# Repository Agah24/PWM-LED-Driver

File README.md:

# PWM-LED-Driver
Here is a KiCad Project for an PWM LED Driver to adjust its brightness

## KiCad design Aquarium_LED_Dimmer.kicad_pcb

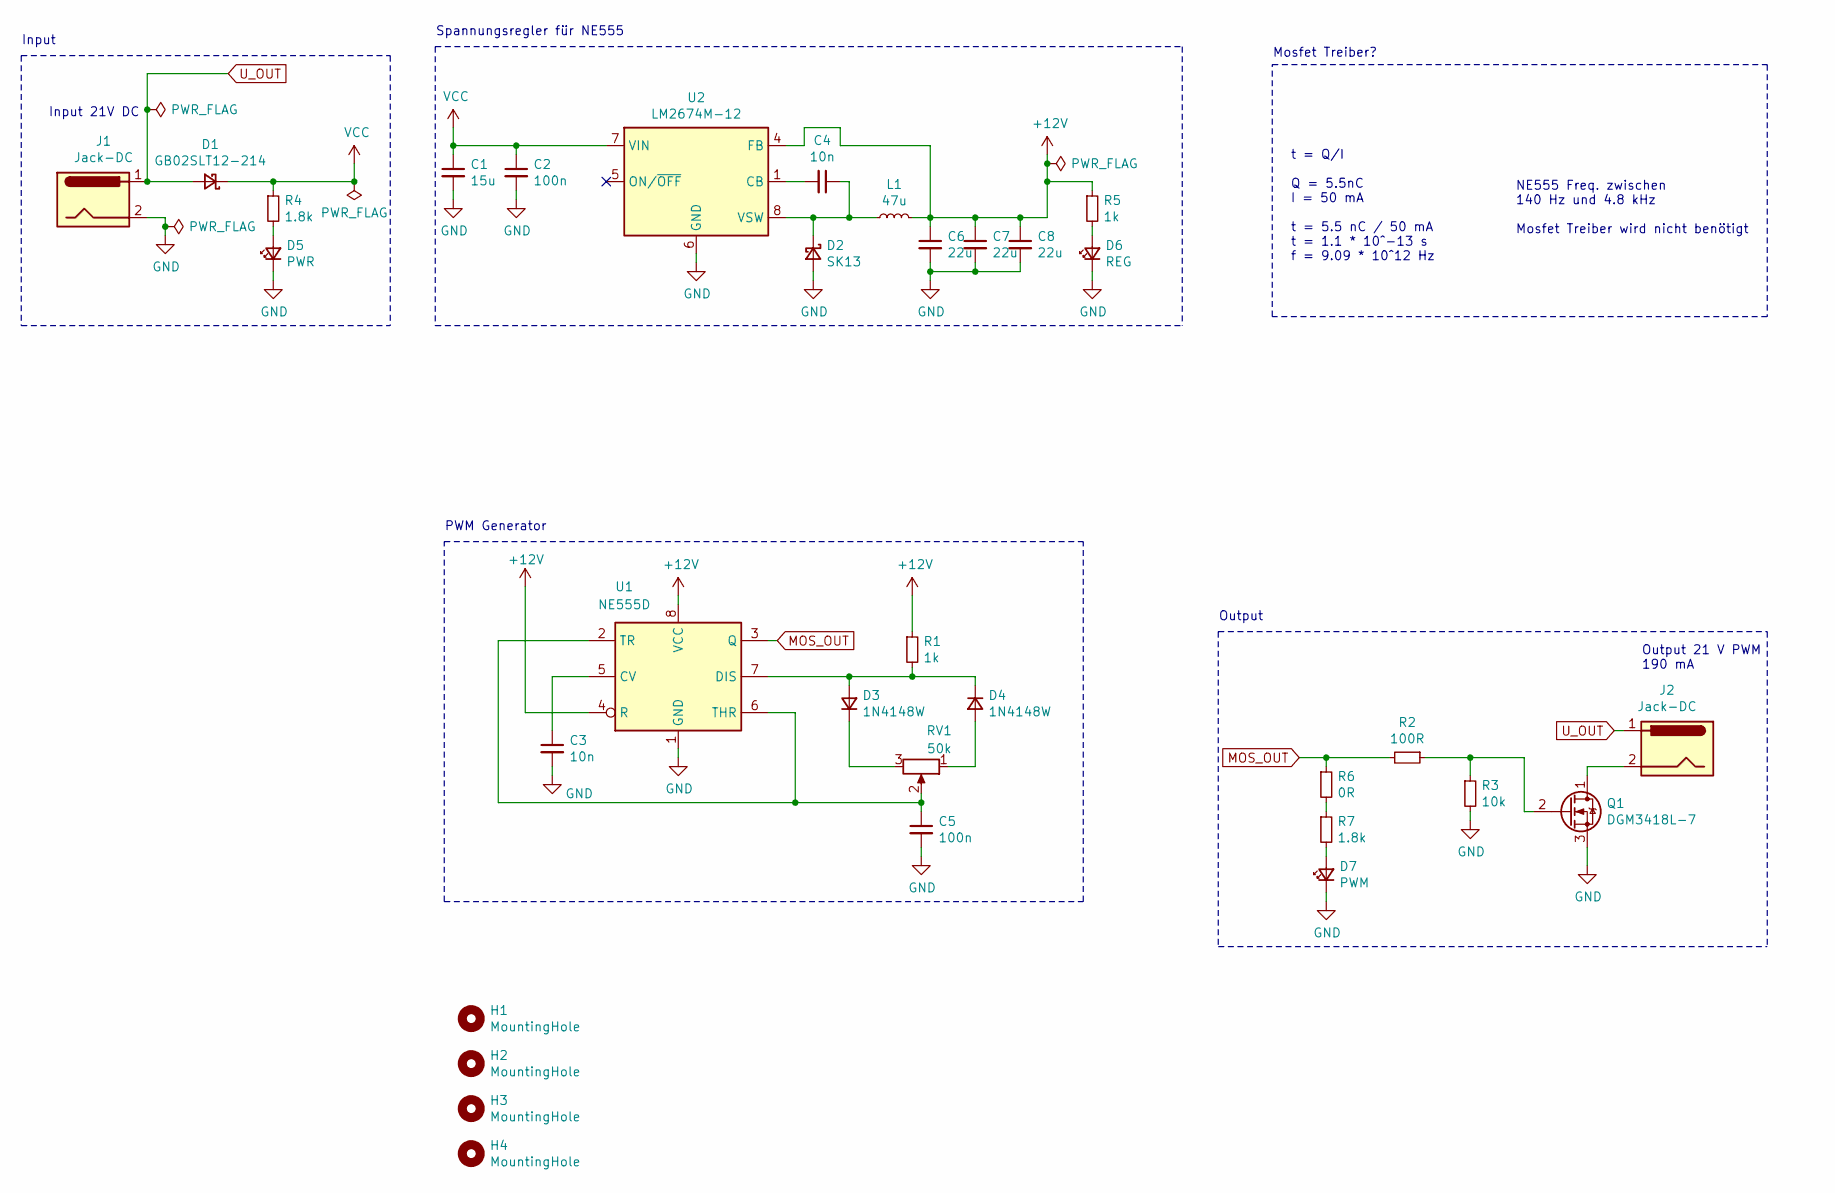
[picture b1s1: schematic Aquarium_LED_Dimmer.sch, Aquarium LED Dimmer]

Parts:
C1: 15u; C_0805_2012Metric
C2, C5: 100n; C_0603_1608Metric
C3, C4: 10n; C_0603_1608Metric
C6, C7, C8: 22u; C_0805_2012Metric
D1: GB02SLT12-214; SSB43L-E3&slash_52T
D2: SK13; SSB43L-E3&slash_52T
D3, D4: 1N4148W; D_SOD-123
D5: PWR; LED_0603_1608Metric
D6: REG; LED_0603_1608Metric
D7: PWM; LED_0603_1608Metric
H1, H2, H3, H4: MountingHole; MountingHole_3.2mm_M3_DIN965_Pad
J1, J2: Jack-DC; BarrelJack_Horizontal
L1: 47u; L_Taiyo-Yuden_NR-60xx
Q1: DGM3418L-7; SOT-23
R1, R5: 1k; R_0603_1608Metric
R2: 100R; R_0603_1608Metric
R3: 10k; R_0603_1608Metric
R4, R7: 1.8k; R_0603_1608Metric
R6: 0R; R_0603_1608Metric
RV1: 50k; Bourns_3362P-503TLF-ND
U1: NE555D; SOIC-8_3.9x4.9mm_P1.27mm
U2: LM2674M-12; SOIC-8_3.9x4.9mm_P1.27mm

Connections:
+12V: C6.1, C7.1, C8.1, L1.2, R1.1, R5.1, U1.4 (R), U1.8 (VCC), U2.4 (FB)
GND: C1.2, C2.2, C3.2, C5.2, C6.2, C7.2, C8.2, D2.2 (A), D5.1 (K), D6.1 (K), D7.1 (K), J1.2, Q1.3 (S), R3.2, U1.1 (GND), U2.2 (NC), U2.3 (NC), U2.6 (GND); also elsewhere on the board
MOS_OUT: R2.2, R6.1, U1.3 (Q)
unnamed: C3.1, U1.5 (CV)
unnamed: C4.1, D2.1 (K), L1.1, U2.8 (VSW)
unnamed: C4.2, U2.1 (CB)
unnamed: C5.1, RV1.2, U1.2 (TR), U1.6 (THR)
unnamed: D3.1 (K), RV1.3
unnamed: D3.2 (A), D4.1 (K), R1.2, U1.7 (DIS)
unnamed: D4.2 (A), RV1.1
unnamed: D5.2 (A), R4.2
unnamed: D6.2 (A), R5.2
unnamed: D7.2 (A), R7.2
unnamed 13: J2.2, Q1.1 (D); also elsewhere on the board
unnamed: Q1.2 (G), R2.1, R3.1
unnamed: R6.2, R7.1
U_OUT: D1.2 (A), J1.1, J2.1; also elsewhere on the board
VCC: C1.1, C2.1, D1.1 (K), R4.1, U2.7 (VIN)

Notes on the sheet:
Input 21V DC
Output 21 V PWM 190 mA
Input
Spannungsregler für NE555
PWM Generator
Output
Mosfet Treiber?
t = Q/I Q = 5.5nC I = 50 mA t = 5.5 nC / 50 mA t = 1.1 * 10^-13 s f = 9.09 * 10^12 Hz
NE555 Freq. zwischen 140 Hz und 4.8 kHz Mosfet Treiber wird nicht benötigt

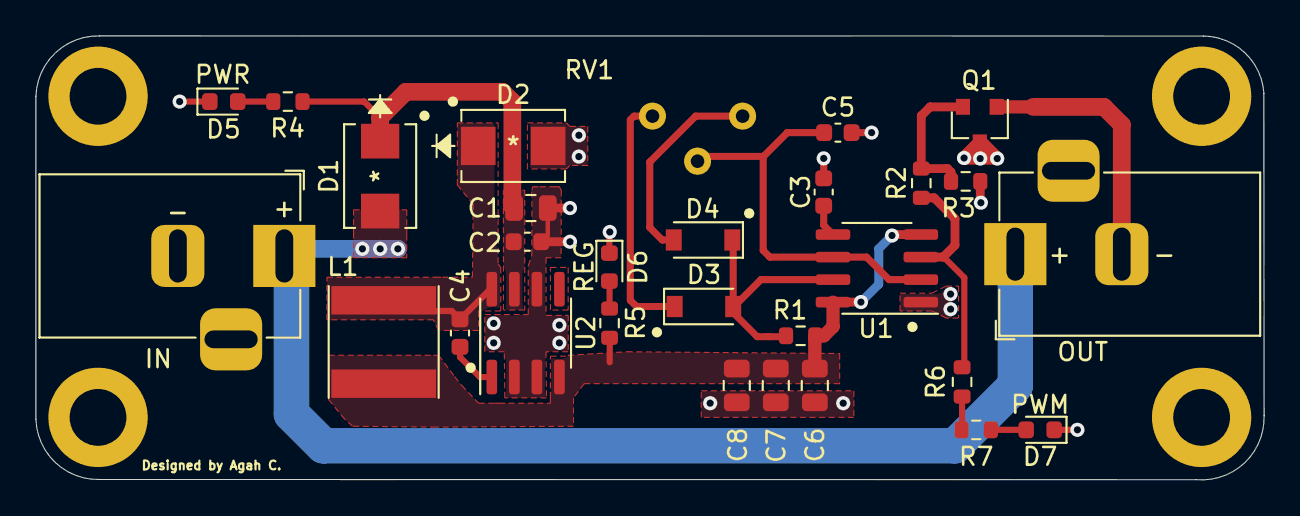
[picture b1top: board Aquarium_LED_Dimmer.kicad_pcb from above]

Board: 2 copper layers, 69.2 x 25.0 mm, 33 parts (0 on the bottom side), 18 nets.

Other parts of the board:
IN: Jack-DC; BarrelJack_Horizontal
OUT: Jack-DC; BarrelJack_Horizontal

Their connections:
GND: IN.2; also elsewhere on the board
unnamed 13: OUT.2; also elsewhere on the board
U_OUT: IN.1, OUT.1; also elsewhere on the board

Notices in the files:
parts and their libraries:
Copyright 2021 Accelerated Designs. All rights reserved.
